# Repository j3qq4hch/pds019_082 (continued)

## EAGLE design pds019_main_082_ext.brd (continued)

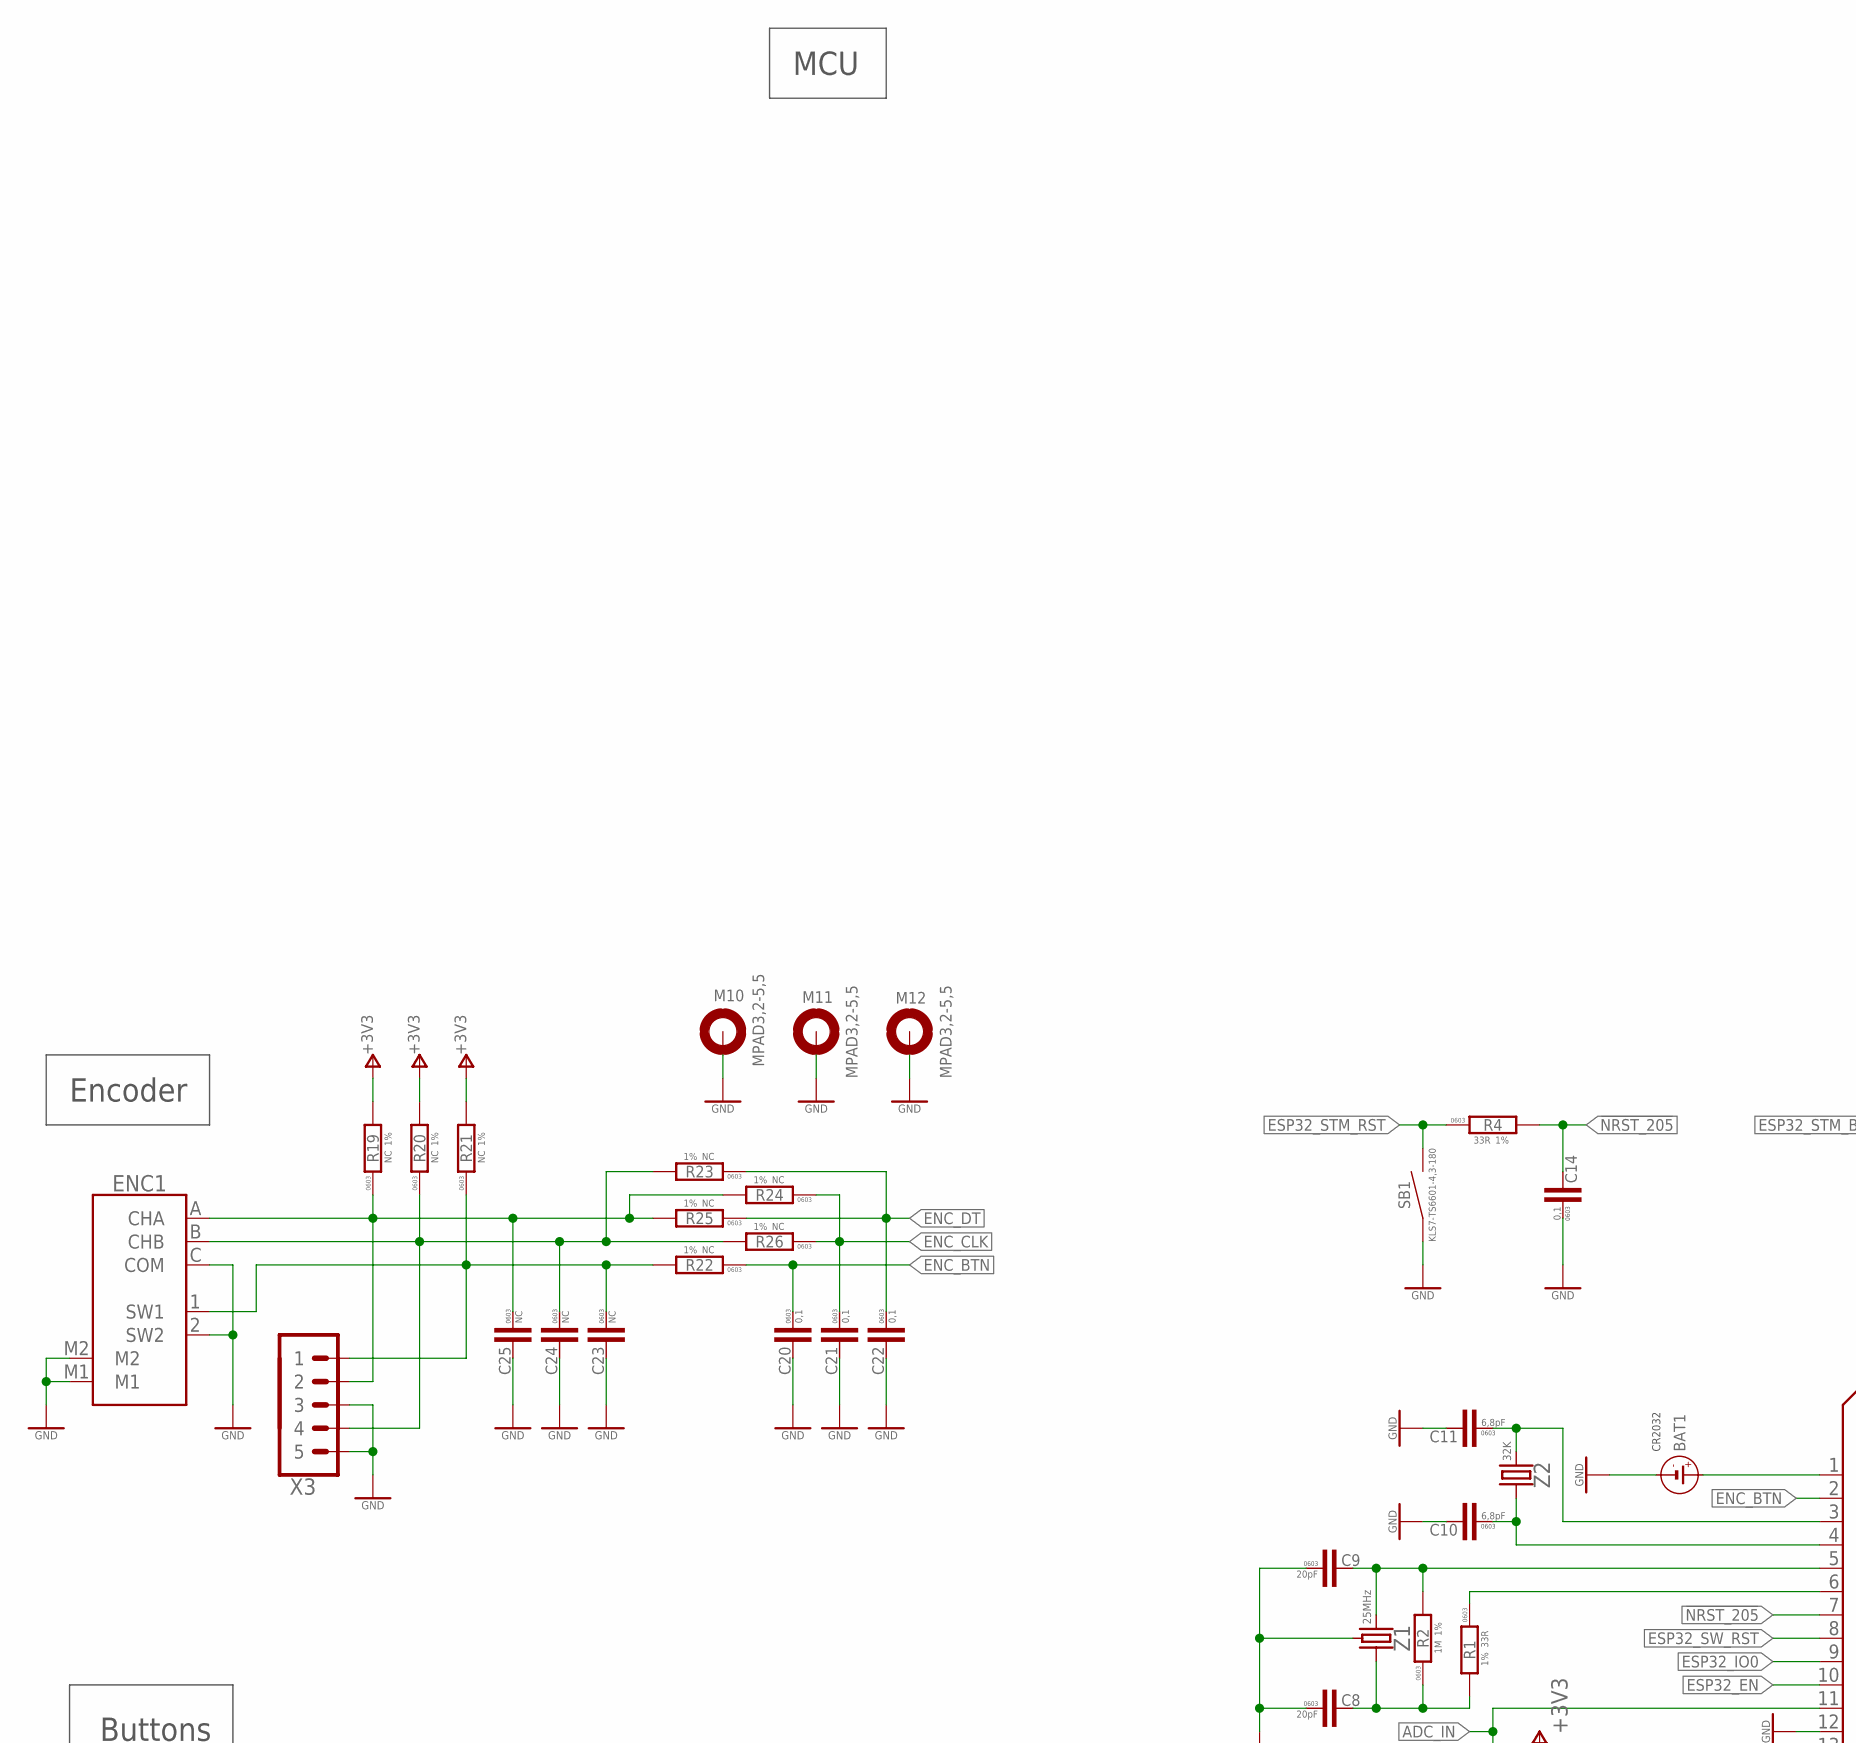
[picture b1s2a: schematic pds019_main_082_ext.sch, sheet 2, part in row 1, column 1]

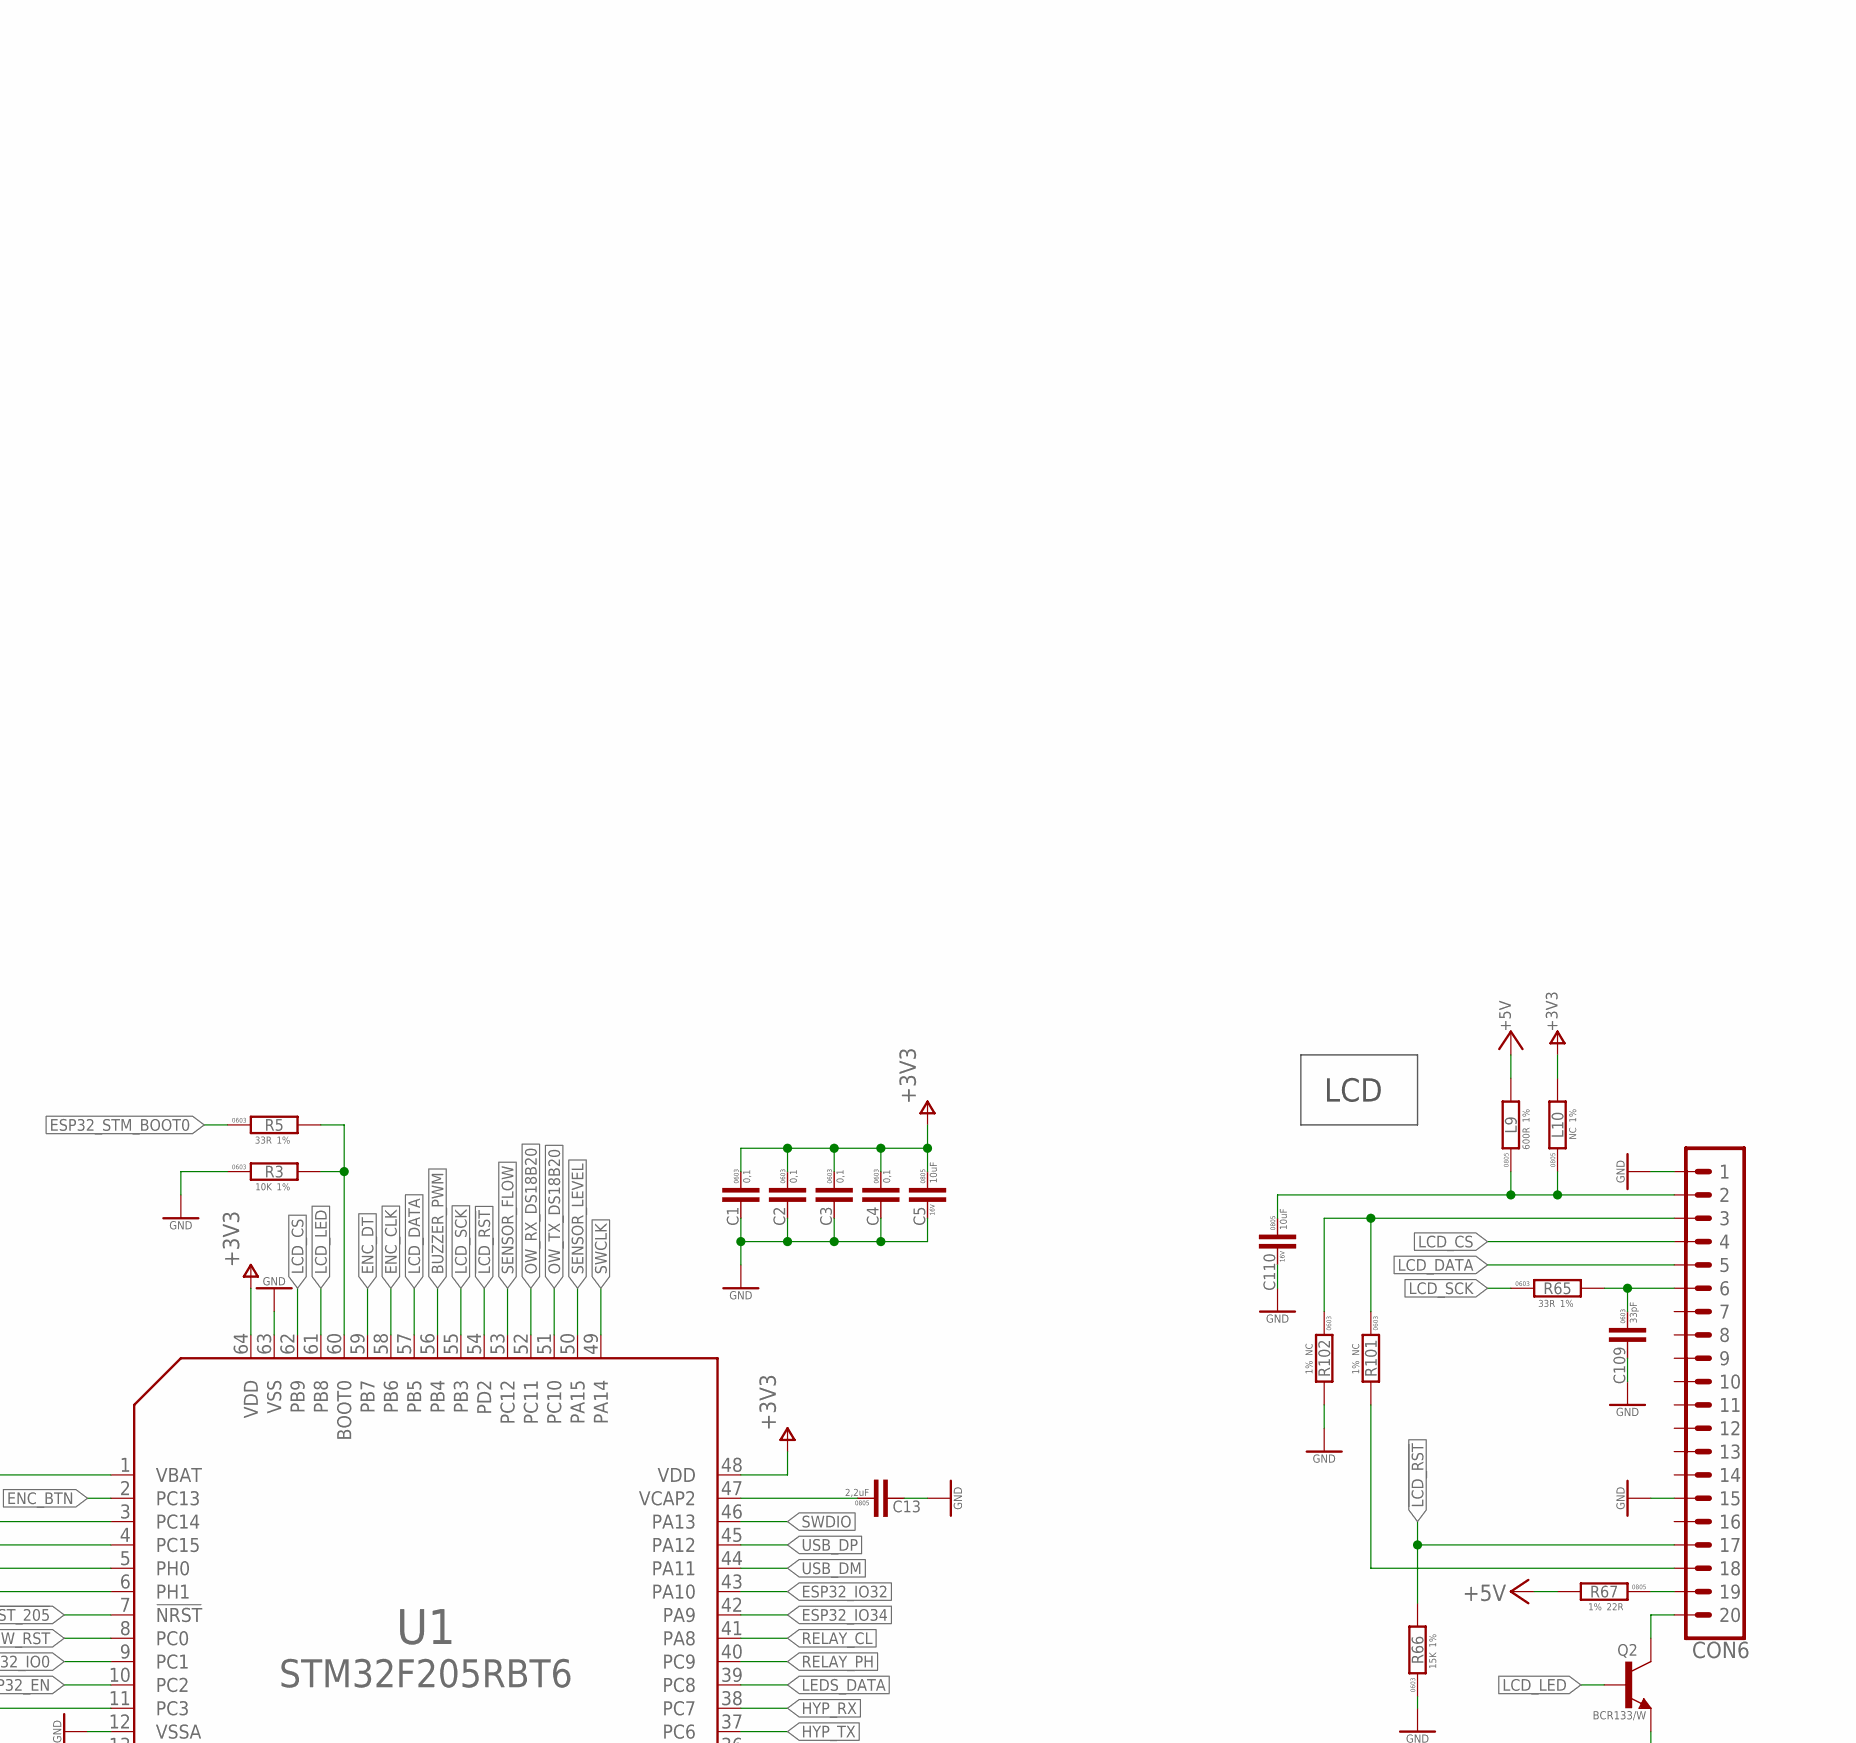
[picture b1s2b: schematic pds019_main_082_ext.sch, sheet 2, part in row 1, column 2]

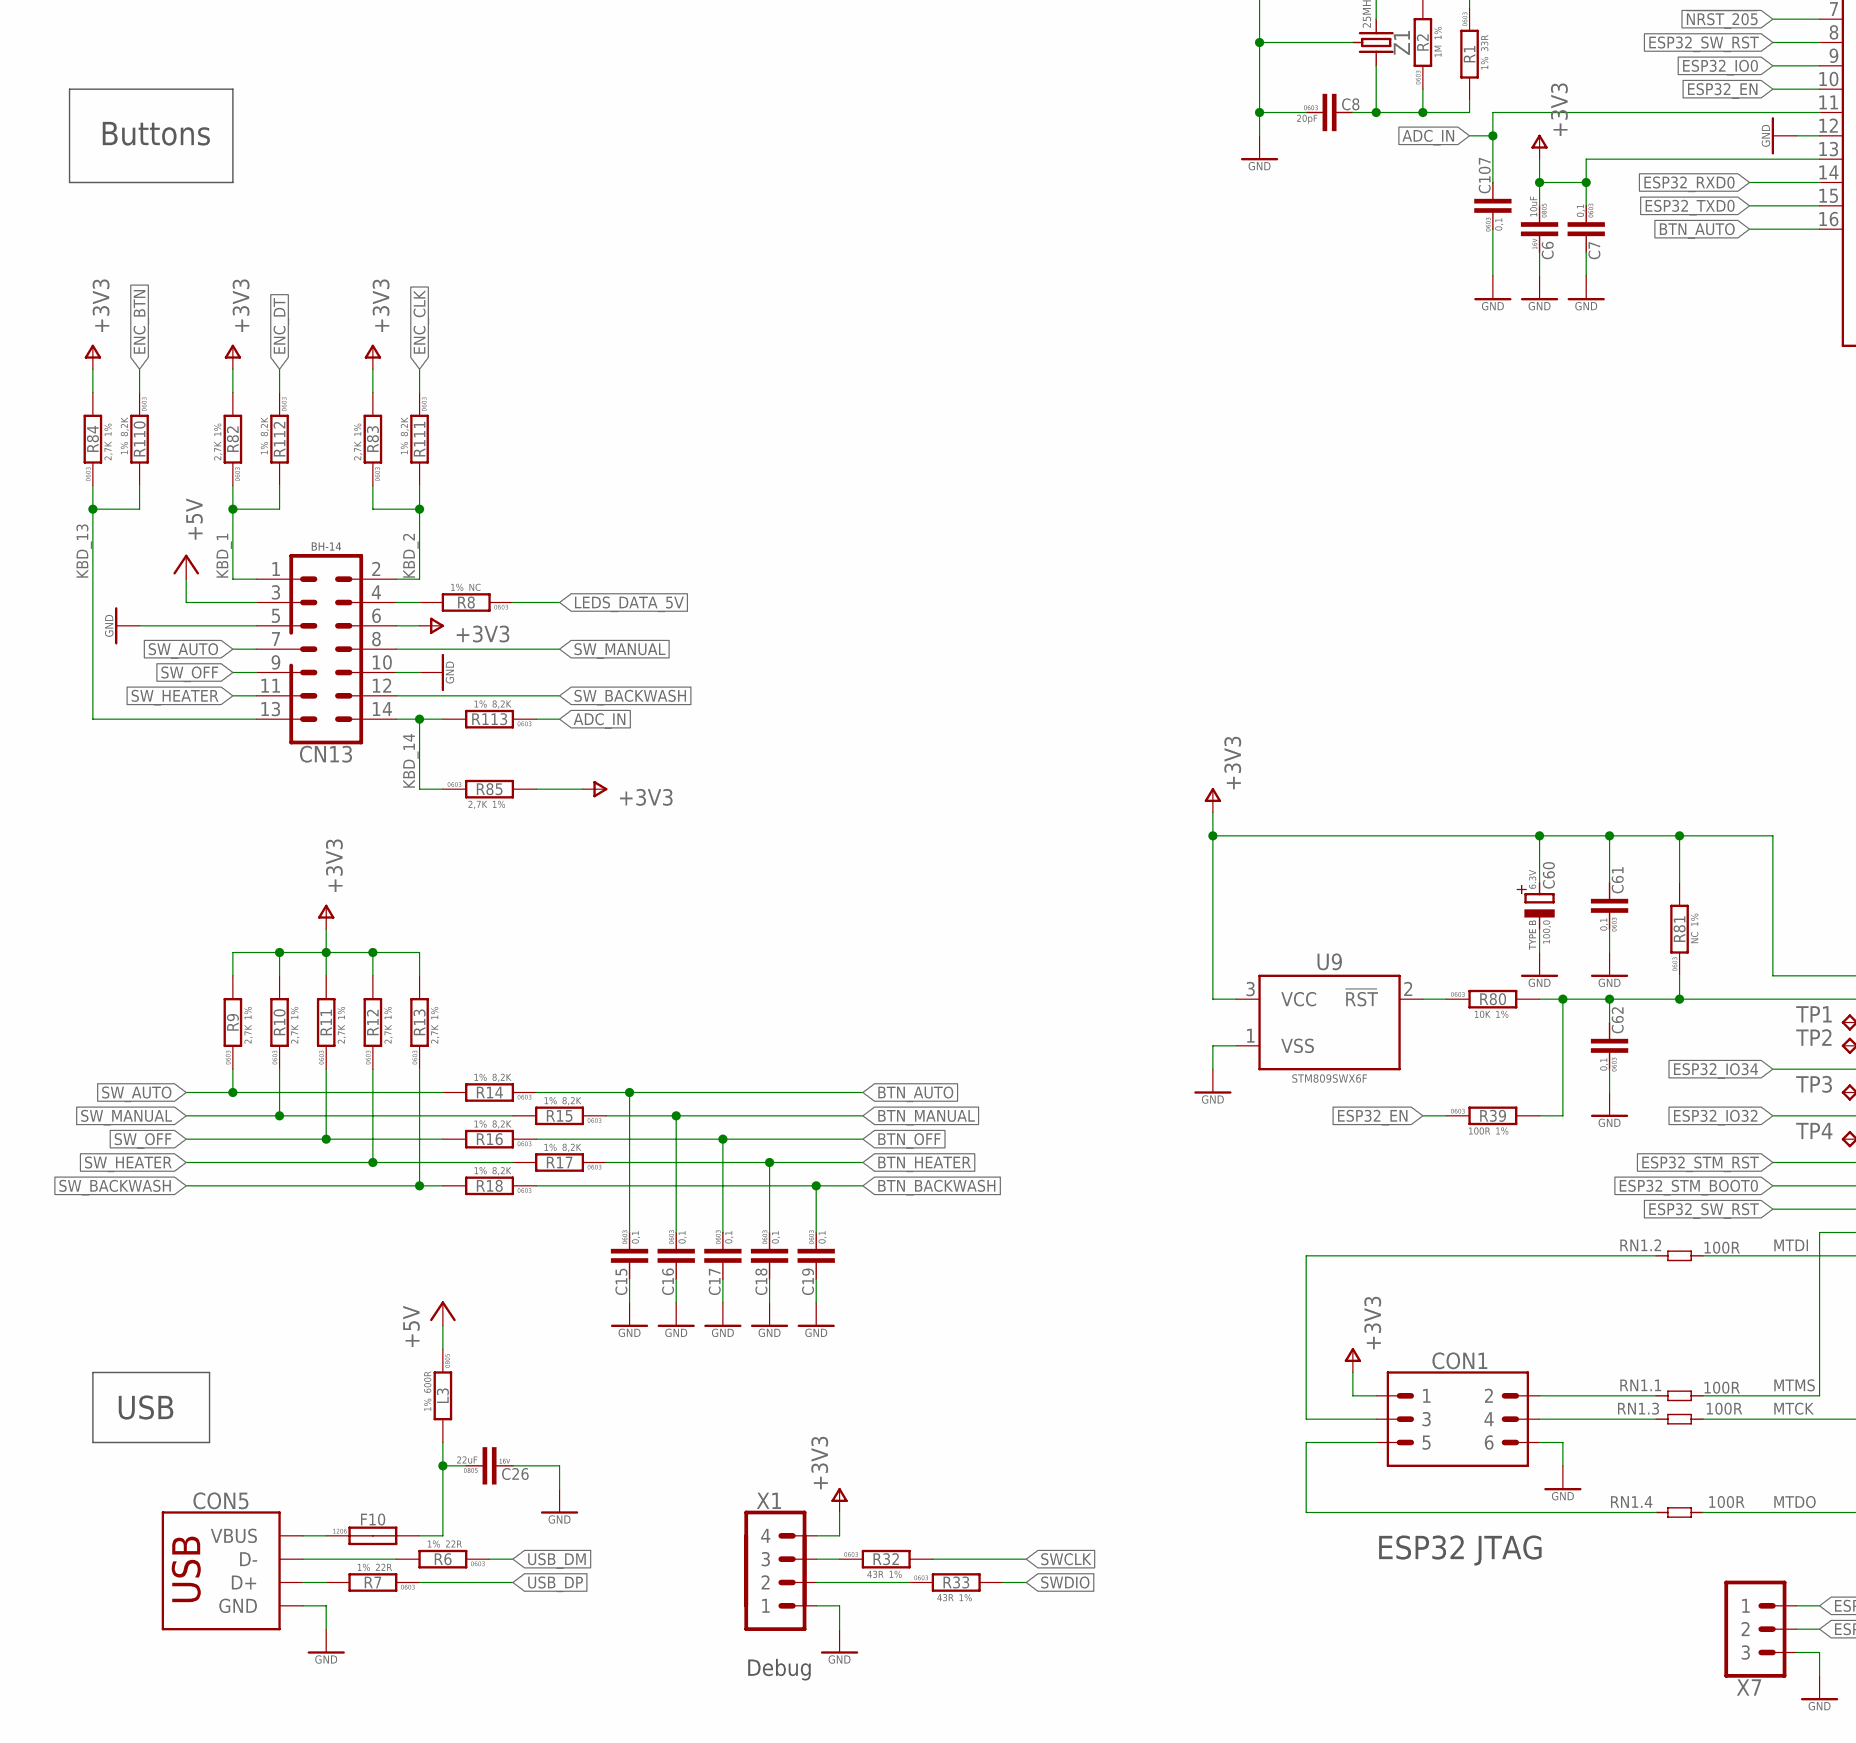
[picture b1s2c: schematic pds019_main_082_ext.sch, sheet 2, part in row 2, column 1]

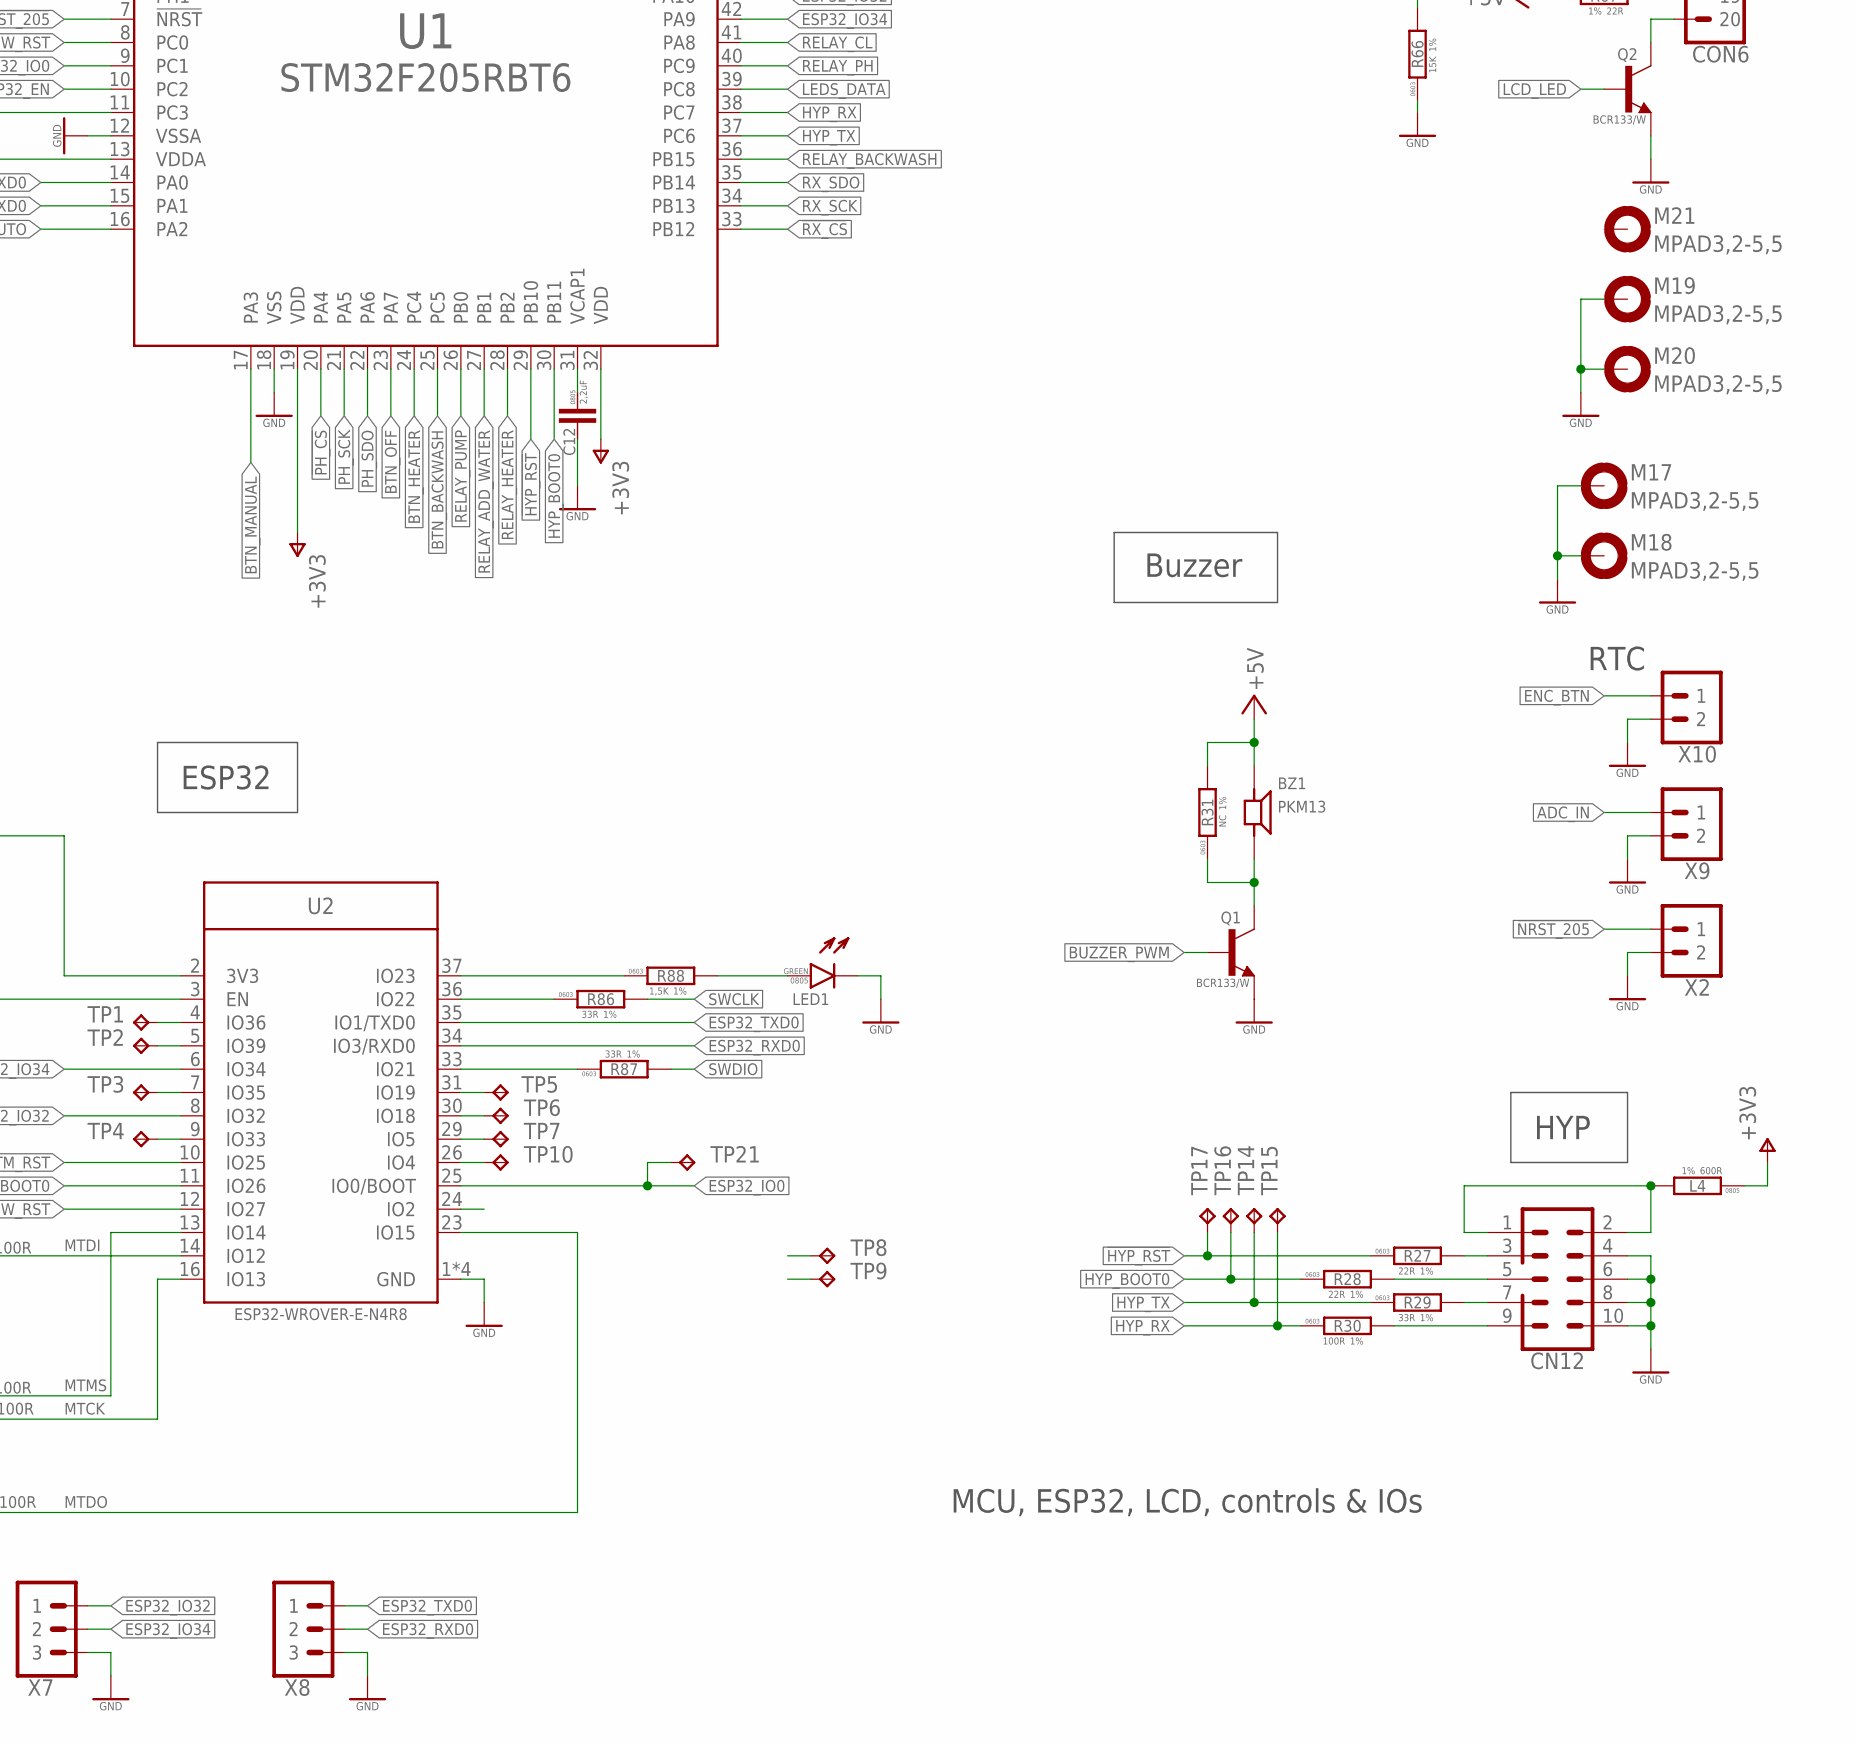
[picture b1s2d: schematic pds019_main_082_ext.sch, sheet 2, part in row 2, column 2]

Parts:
BAT1: BATTERY-L-KLS5-CR2032-01; CR2032H
BZ1: PKM13
C1, C2, C3, C4, C7, C14, C15, C16, C17, C18, C19, C20, C21, C22, C61, C62, C107: 0,1; C0603
C5, C6, C110: 10uF; C0805; VOLTAGE 16V
C8, C9: 20pF; C0603
C10, C11: 6,8pF; C0603
C12, C13: 2,2uF; C0805
C23, C24, C25: NC; C0603
C26: 22uF; C0805; VOLTAGE 16V
C60: 100,0; CTANT_B; VOLTAGE 6.3V
C109: 33pF; C0603
CN12: BH-10; IDC_2X05
CN13: BH14; IDC_2X07
CON1: PINHEAD_2X03-PTH-2.54; 2X03-PTH-2.54
CON5: USB-A-KLS1-191; KLS1-191-4P-0.7
CON6: PINHEAD_1X20-2.54-MALE-LONG; 1X20-PTH-2.54-LONG
ENC1: PEC12R-4XXXF-S; PEC12R-4XXXF-SXXXX
F10: FUSE-1206; F1206
L3, L4, L9: 600R; R0805
L10: NC; R0805
LED1: LED-0805; LED0805
M10, M11, M12, M17, M18, M19, M20, M21: MPAD3,2-5,5; MPAD_3,2_5,5
Q1: NC; SOT23B-3
Q2: BCR133; SOT23B-3
R1, R4, R5, R29, R65, R86, R87: 33R; R0603
R2: 1M; R0603
R3, R80: 10K; R0603
R6, R7, R27, R28: 22R; R0603
R8, R19, R20, R21, R22, R23, R24, R25, R26, R31, R81, R101, R102: NC; R0603
R9, R10, R11, R12, R13, R82, R83, R84, R85: 2,7K; R0603
R14, R15, R16, R17, R18, R110, R111, R112, R113: 8,2K; R0603
R30, R39: 100R; R0603
R32, R33: 43R; R0603
R66: 15K; R0603
R67: 22R; R0805
R88: 1,5K; R0603
RN1: 100R; RN_YC164
SB1: KLS7-TS6601-4,3-180; SW4-6.0X6.0X5.0MM
TP1, TP2, TP3, TP4: TPTP18R; TP18R
TP5, TP6, TP7, TP8, TP9, TP10, TP14, TP15, TP16, TP17, TP21: TPTP16R; TP16R
U1: STM32F2xxR; TQFP64
U2: ESP32-WROVER-(I)E; ESP32-WROVER-E
U9: MAX809S; SOT23B-3
X1: PINHEAD_1X04-2.54; 1X04-PTH-2.54
X2, X9, X10: PINHEAD_1X02-2.54; 1X02-PTH-2.54
X3: PINHEAD_1X05-2.54; 1X05-PTH-2.54
X7, X8: PINHEAD_1X03-2.54; 1X03-PTH-2.54
Z1: 25MHz; OSCILLATOR-3.2X2.5-4P
Z2: 32K; 32X15

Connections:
!HYP_RST: R27.1, TP17.TP, U1.29 (PB10)
!LCD_RST: CON6.17, R66.2, U1.54 (PD2)
!NRST_205: C14.2, R4.2, U1.7 (!NRST), X2.1
!PH_CS: U1.20 (PA4); also elsewhere on the board
!RX_CS: U1.33 (PB12); also elsewhere on the board
+3V3: C1.1, C2.1, C3.1, C4.1, C5.1, C6.1, C7.1, C60.+, C61.2, CN13.6, CON1.1, L4.1, L10.2, R9.2, R10.2, R11.2, R12.2, R13.2, R19.2, R20.2, R21.2, R81.2, R82.2, R83.2, R84.2, R85.2, U1.13 (VDDA), U1.19 (VDD), U1.32 (VDD), U1.48 (VDD), U1.64 (VDD), U2.2 (3V3), U9.3 (VCC), X1.4; also elsewhere on the board
+5V: BZ1.B+ (1), CN13.3, L3.1, L9.2, R31.2, R67.2; also elsewhere on the board
ADC_IN: C107.2, R113.1, U1.11 (PC3), X9.1
BOOT0_205: R3.2, R5.2, U1.60 (BOOT0)
BTN_AUTO: C15.1, R14.1, U1.16 (PA2)
BTN_BACKWASH: C19.1, R18.1, U1.25 (PC5)
BTN_HEATER: C18.1, R17.1, U1.24 (PC4)
BTN_MANUAL: C16.1, R15.1, U1.17 (PA3)
BTN_OFF: C17.1, R16.1, U1.23 (PA7)
BUZZER_PWM: Q1.1 (B), U1.56 (PB4); also elsewhere on the board
ENC_A: C25.1, ENC1.A (CHA), R19.1, R24.2, R25.2, X3.2
ENC_B: C24.1, ENC1.B (CHB), R20.1, R23.2, R26.2, X3.4
ENC_BTN: C20.1, R22.1, R110.1, U1.2 (PC13), X10.1
ENC_CLK: C21.1, R24.1, R26.1, R111.1, U1.58 (PB6)
ENC_DT: C22.1, R23.1, R25.1, R112.1, U1.59 (PB7)
ENC_SW: C23.1, ENC1.1 (SW1), R21.1, R22.2, X3.1
ESP32_EN: R39.1, U1.10 (PC2)
ESP32_IO0: TP21.TP, U1.9 (PC1), U2.25 (IO0/BOOT)
ESP32_IO32: U1.43 (PA10), U2.8 (IO32), X7.1
ESP32_IO34: U1.42 (PA9), U2.6 (IO34), X7.2
ESP32_RXD0: U1.14 (PA0), U2.34 (IO3/RXD0), X8.2
ESP32_STM_BOOT0: R5.1, U2.11 (IO26)
ESP32_STM_RST: R4.1, SB1.2, SB1.3 (2), U2.10 (IO25)
ESP32_STM_SWCLK: R86.1, U2.36 (IO22)
ESP32_STM_SWDIO: R87.1, U2.33 (IO21)
ESP32_SW_RST: U1.8 (PC0), U2.12 (IO27)
ESP32_TXD0: U1.15 (PA1), U2.35 (IO1/TXD0), X8.1
GND: BAT1.- (NEGATIVE), C1.2, C2.2, C3.2, C4.2, C5.2, C6.2, C7.2, C8.1, C9.1, C10.2, C11.2, C12.2, C13.2, C14.1, C15.2, C16.2, C17.2, C18.2, C19.2, C20.2, C21.2, C22.2, C23.2, C24.2, C25.2, C26.2, C60.-, C61.1, C62.1, C107.1, C109.2, C110.2, CN12.4, CN12.6, CN12.8, CN12.10, CN13.5, CN13.10, CON1.6, CON5.4 (GND), CON5.SH1 (GND), CON5.SH2 (GND), CON5.SH3 (GND), CON5.SH4 (GND), CON6.1, CON6.15, ENC1.2 (SW2), ENC1.C (COM), ENC1.M1, ENC1.M2, LED1.C, M10.1, M11.1, M12.1, M17.1, M18.1, M19.1, M20.1, Q1.2 (E), Q2.2 (E), R3.1, R66.1, R102.2, SB1.1, SB1.4 (1), U1.12 (VSSA), U1.18 (VSS), U1.63 (VSS), U2.1 (GND), U2.15 (GND), U2.38 (GND), U2.39 (GND), U9.1 (VSS), X1.1, X2.2, X3.3, X3.5, X7.3, X8.3, X9.2, X10.2, Z1.2 (GND), Z1.4 (GND); also elsewhere on the board
HYP_BOOT0: R28.1, TP16.TP, U1.30 (PB11)
HYP_RX: R30.1, TP15.TP, U1.38 (PC7)
HYP_TX: R29.1, TP14.TP, U1.37 (PC6)
KBD_1: CN13.1, R82.1, R112.2
KBD_2: CN13.2, R83.1, R111.2
KBD_13: CN13.13, R84.1, R110.2
KBD_14: CN13.14, R85.1, R113.2
LCD_CS: CON6.4, U1.62 (PB9)
LCD_DATA: CON6.5, U1.57 (PB5)
LCD_LED: Q2.1 (B), U1.61 (PB8)
LCD_LED_A: CON6.19, R67.1
LCD_LED_K: CON6.20, Q2.3 (C)
LCD_SCK: R65.1, U1.55 (PB3)
LCD_V0: CON6.3, R101.1, R102.1
LCD_VEE: CON6.18, R101.2
LEDS_DATA: U1.39 (PC8); also elsewhere on the board
LEDS_DATA_5V: R8.1; also elsewhere on the board
MTCK: RN1.6 (2), U2.16 (IO13)
MTDI: RN1.7 (2), U2.14 (IO12)
MTDO: RN1.5 (2), U2.23 (IO15)
MTMS: RN1.8 (2), U2.13 (IO14)
unnamed: CN12.1, CN12.2, L4.2
unnamed: CN12.3, R27.2
unnamed: CN12.5, R28.2
unnamed: CN12.7, R29.2
unnamed: CN12.9, R30.2
unnamed: R88.1, U2.37 (IO23)
unnamed: LED1.A, R88.2
unnamed: C109.1, CON6.6, R65.2
unnamed: R32.1, X1.3
unnamed: R33.1, X1.2
unnamed: R80.1, U9.2 (!RST)
unnamed: CN13.4, R8.2
unnamed: C110.1, CON6.2, L9.1, L10.1
unnamed: C62.2, R39.2, R80.2, R81.1, U2.3 (EN)
unnamed: TP1.TP, U2.4 (IO36)
unnamed: TP2.TP, U2.5 (IO39)
unnamed: TP3.TP, U2.7 (IO35)
unnamed: TP4.TP, U2.9 (IO33)
unnamed: TP5.TP, U2.31 (IO19)
unnamed: TP6.TP, U2.30 (IO18)
unnamed: TP7.TP, U2.29 (IO5)
unnamed: TP10.TP, U2.26 (IO4)
unnamed: C12.1, U1.31 (VCAP1)
unnamed: C13.1, U1.47 (VCAP2)
unnamed: C8.2, R1.2, R2.1, Z1.1
unnamed: CON5.1 (VBUS), F10.P$1 (1)
unnamed: C26.1, F10.P$2 (2), L3.2
unnamed: CON1.5, RN1.4 (1)
unnamed: CON5.2 (D-), R6.2
unnamed: CON5.3 (D+), R7.2
unnamed: CON1.2, RN1.1
unnamed: BZ1.B- (2), Q1.3 (C), R31.1
unnamed: CON1.3, RN1.2 (1)
unnamed: CON1.4, RN1.3 (1)
OSC_IN: C9.2, R2.2, U1.5 (PH0), Z1.3 (2)
OSC_OUT: R1.1, U1.6 (PH1)
OW_RX_DS18B20: U1.52 (PC11); also elsewhere on the board
OW_TX_DS18B20: U1.51 (PC10); also elsewhere on the board
PH_SCK: U1.21 (PA5); also elsewhere on the board
PH_SDO: U1.22 (PA6); also elsewhere on the board
RELAY_ADD_WATER: U1.27 (PB1); also elsewhere on the board
RELAY_BACKWASH: U1.36 (PB15); also elsewhere on the board
RELAY_CL: U1.41 (PA8); also elsewhere on the board
RELAY_HEATER: U1.28 (PB2); also elsewhere on the board
RELAY_PH: U1.40 (PC9); also elsewhere on the board
RELAY_PUMP: U1.26 (PB0); also elsewhere on the board
RTC_VBAT: BAT1.+ (POSITIVE), U1.1 (VBAT)
RTC_XTAL_IN: C11.1, U1.3 (PC14), Z2.P$2 (2)
RTC_XTAL_OUT: C10.1, U1.4 (PC15), Z2.P$1 (1)
RX_SCK: U1.34 (PB13); also elsewhere on the board
RX_SDO: U1.35 (PB14); also elsewhere on the board
SENSOR_FLOW: U1.53 (PC12); also elsewhere on the board
SENSOR_LEVEL: U1.50 (PA15); also elsewhere on the board
SWCLK: R32.2, R86.2, U1.49 (PA14)
SWDIO: R33.2, R87.2, U1.46 (PA13)
SW_AUTO: CN13.7, R9.1, R14.2
SW_BACKWASH: CN13.12, R13.1, R18.2
SW_HEATER: CN13.11, R12.1, R17.2
SW_MANUAL: CN13.8, R10.1, R15.2
SW_OFF: CN13.9, R11.1, R16.2
USB_DM: R6.1, U1.44 (PA11)
USB_DP: R7.1, U1.45 (PA12)

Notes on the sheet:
Encoder
Debug
LCD
Buzzer
ESP32
Buttons
USB
ESP32 JTAG
MCU, ESP32, LCD, controls & IOs
HYP
RTC
MCU
